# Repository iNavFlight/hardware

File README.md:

INAV Hardware
=============

This repository contains hardware designs made by the INAV team.
Each directory contains a different project.

[PowerSwitch](PowerSwitch): A high side power switch that
can be turned on or off by the flight controller using PINIO:

Includes a KiBot script to generate Gerbers/BOM/CPL files ready
to send to JLCPCB for fabrication. You can use
[KiKkit](https://github.com/yaqwsx/KiKit/) to easily panelize
the boards:

```
kikit panelize grid --space 2 --gridsize 5 3 --tabwidth 3 \
      --tabheight 3 --htabs 2 --vtabs 1 --mousebites 0.5 \
      1 0.25 --radius 1 PowerSwitch.kicad_pcb panel.kicad_pcb
```

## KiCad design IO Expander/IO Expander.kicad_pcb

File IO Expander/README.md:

# INAV I2C IO Expander board

INAV I2C IO Expander board offers 8 digital outputs. 

* All elements are THT for easy soldering by beginners
* 36x36mm PCB with 30.5x30.5mm mounting holes fits on top of most flight controllers
* Each channel can be loaded to around 300mA on 3.3V
* Switching is done on the low side
* In case of inductive load, COM port has to be connected to the Vcc
* Max voltage ULN2803 can handle is 50V. It is 8S ready, however 12-16V is recommended
* Connects via I2C to any INAV compatible flight controller
* Supported in INAV 2.6 via Logic Conditions in Programming Framework
* Buttons are not yet supported by INAV

## Example usage

## BOM

* 1x PCF8574 THT
* 1x ULN2803A THT
* 2x Tactile button

PCB can be ordered via [OSH Park](https://oshpark.com/shared_projects/GNc1dy58)

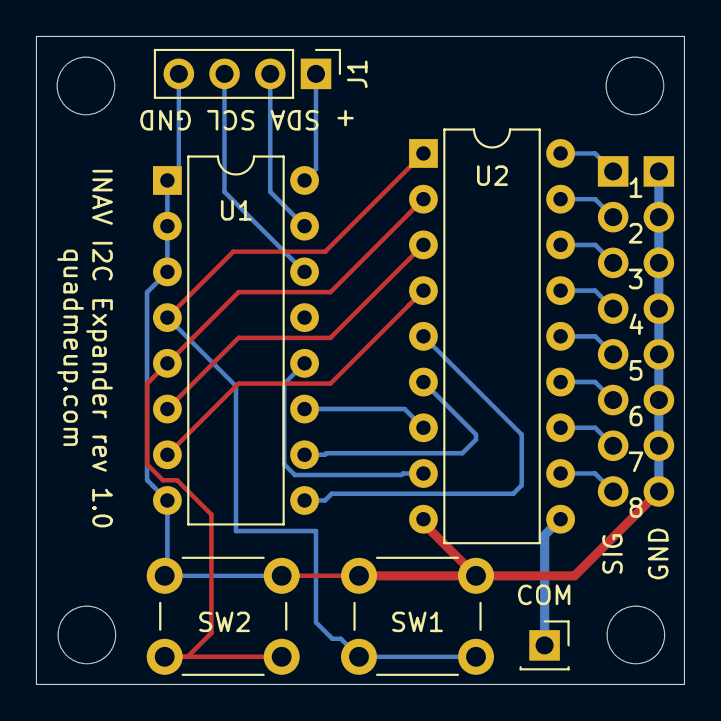
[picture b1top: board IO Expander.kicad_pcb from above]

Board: 2 copper layers, 36.0 x 36.0 mm, 8 parts (0 on the bottom side), 21 nets.

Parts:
COM: Conn_01x01; PinSocket_1x01_P2.54mm_Vertical
J1: Conn_01x04; PinHeader_1x04_P2.54mm_Vertical
J2, J3: Conn_01x08; PinSocket_1x08_P2.54mm_Vertical
SW1, SW2: SW_Push; SW_PUSH_6mm_H5mm
U1: PCF8574A; DIP-16_W7.62mm
U2: ULN2803A; DIP-18_W7.62mm

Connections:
unnamed: J1.1, U1.16
unnamed: J1.2, U1.15
unnamed: J1.3, U1.14
unnamed: J1.4, J3.1, J3.2, J3.3, J3.4, J3.5, J3.6, J3.7, J3.8, SW1.2, SW2.2, U1.1, U1.2, U1.3, U1.8, U2.9
unnamed: J2.1, U2.18
unnamed: J2.2, U2.17
unnamed: J2.3, U2.16
unnamed: J2.4, U2.15
unnamed: J2.5, U2.14
unnamed: J2.6, U2.13
unnamed: J2.7, U2.12
unnamed: J2.8, U2.11
unnamed: COM.1, U2.10
unnamed: SW1.1, U1.4, U2.1
unnamed: SW2.1, U1.5, U2.2
unnamed: U1.6, U2.3
unnamed: U1.7, U2.4
unnamed: U1.9, U2.5
unnamed: U1.10, U2.6
unnamed: U1.11, U2.7
unnamed: U1.12, U2.8

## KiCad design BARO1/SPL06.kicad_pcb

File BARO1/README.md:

INAV BARO1
=================

Barometer board with optional pull-ups, using an SPL06.

## Bill of Materials

- 2x 0603 100n capacitor
- 1x LGA8 SPL06-001
- 2x 0603 10k resistor (optional, skip if the I2C master has adequate pull-ups)
- 1x 0603 100k resistor (optional, needed for alternative I2C addr)

## Building this project

Soldering the SPL06 with an iron can be tricky. Use hot air/reflow oven/hot plate instead. Passives are 0603, so easily doable with
just an iron.

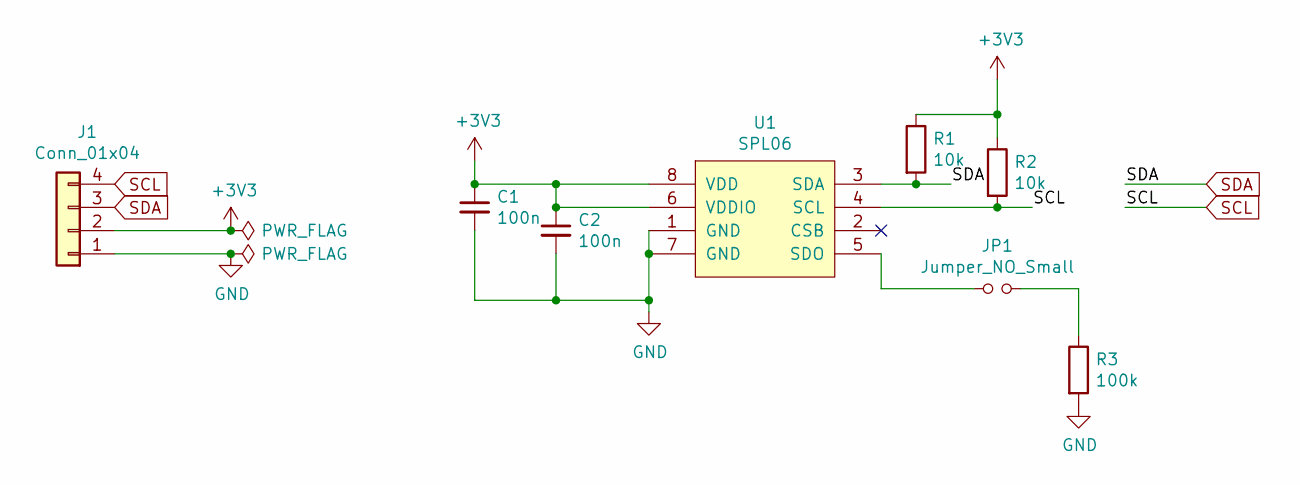
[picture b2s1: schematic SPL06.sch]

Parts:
C1, C2: 100n; C_0603_1608Metric
J1: Conn_01x04; PinHeader_1x04_P2.54mm_Vertical
JP1: Jumper_NO_Small; SolderJumper-2_P1.3mm_Open_TrianglePad1.0x1.5mm
R1, R2: 10k; R_0603_1608Metric
R3: 100k; R_0603_1608Metric
U1: SPL06; Bosch_LGA-8_2x2.5mm_P0.65mm_ClockwisePinNumbering

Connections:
+3V3: C1.1, C2.1, J1.2, R1.1, R2.1, U1.6 (VDDIO), U1.8 (VDD)
GND: C1.2, C2.2, J1.1, R3.2, U1.1 (GND), U1.7 (GND)
unnamed: JP1.1, U1.5 (SDO)
unnamed: JP1.2, R3.1
SCL: J1.4, R2.2, U1.4 (SCL)
SDA: J1.3, R1.2, U1.3 (SDA)

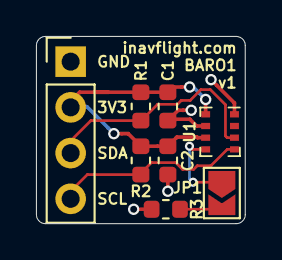
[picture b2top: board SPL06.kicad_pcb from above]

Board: 2 copper layers, 11.6 x 10.4 mm, 8 parts (0 on the bottom side), 6 nets.

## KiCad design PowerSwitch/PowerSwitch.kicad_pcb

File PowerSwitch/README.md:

INAV Power Switch
=================

High side power switch that can be controlled by the flight
controller used PINIO.

Switching on the high side (instead of the simpler low side) is
useful for devices that must stay at exactly the same ground
potential (e.g. camera and VTX).

## Bill of Materials

- 2x 0603 6k8 resistor
- 1x 0603 47k resistor
- 1x 0603 10k resistor
- 1x SOT23 AO3400 N-Channel MOSFET
- 1x SOT23 AO3401 P-Channel MOSFET

## Building this project

All components can easily be soldered with a soldering iron,
just use 0.6mm solder and a fine tip.

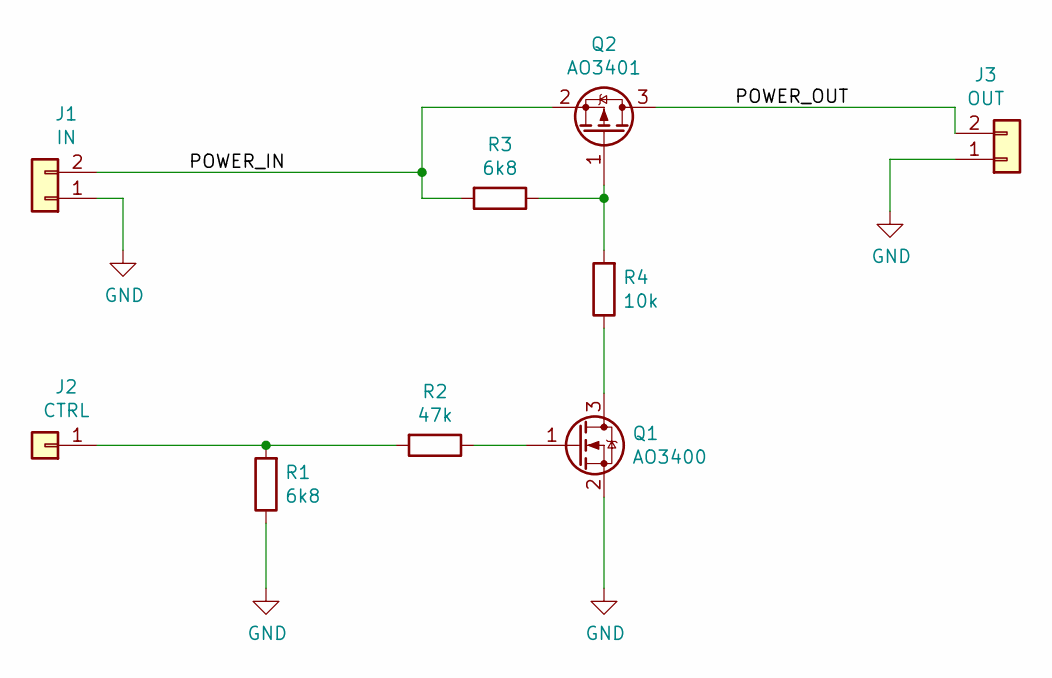
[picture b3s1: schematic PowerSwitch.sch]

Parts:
J1: IN; PadHeader_1x02_P2.54mm
J2: CTRL; PadHeader_1x01_P2.54mm
J3: OUT; PadHeader_1x02_P2.54mm
Q1: AO3400; SOT-23
Q2: AO3401; SOT-23
R1, R3: 6k8; R_0603_1608Metric_Pad1.05x0.95mm_HandSolder
R2: 47k; R_0603_1608Metric_Pad1.05x0.95mm_HandSolder
R4: 10k; R_0603_1608Metric_Pad1.05x0.95mm_HandSolder

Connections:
/POWER_IN: J1.2, Q2.2 (S), R3.2
/POWER_OUT: J3.2, Q2.3 (D)
GND: J1.1, J3.1, Q1.2 (S), R1.1
unnamed: J2.1, R1.2, R2.2
unnamed: Q1.1 (G), R2.1
unnamed: Q1.3 (D), R4.1
unnamed: Q2.1 (G), R3.1, R4.2

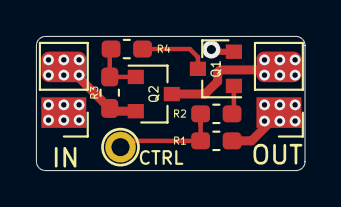
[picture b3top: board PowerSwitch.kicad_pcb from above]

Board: 2 copper layers, 14.9 x 7.5 mm, 10 parts (1 on the bottom side), 7 nets.

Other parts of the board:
LOGO: LOGO_INAV

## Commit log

2019-07-27 Add PowerSwitch project
    High side power switch controlled via PINIO
2019-10-16 Add BARO1 board
    Barometer breakout using SPL06 with optional pullups and I2C
    address selector
2020-08-20 IO Expander
2021-09-26 Add KiBot script
